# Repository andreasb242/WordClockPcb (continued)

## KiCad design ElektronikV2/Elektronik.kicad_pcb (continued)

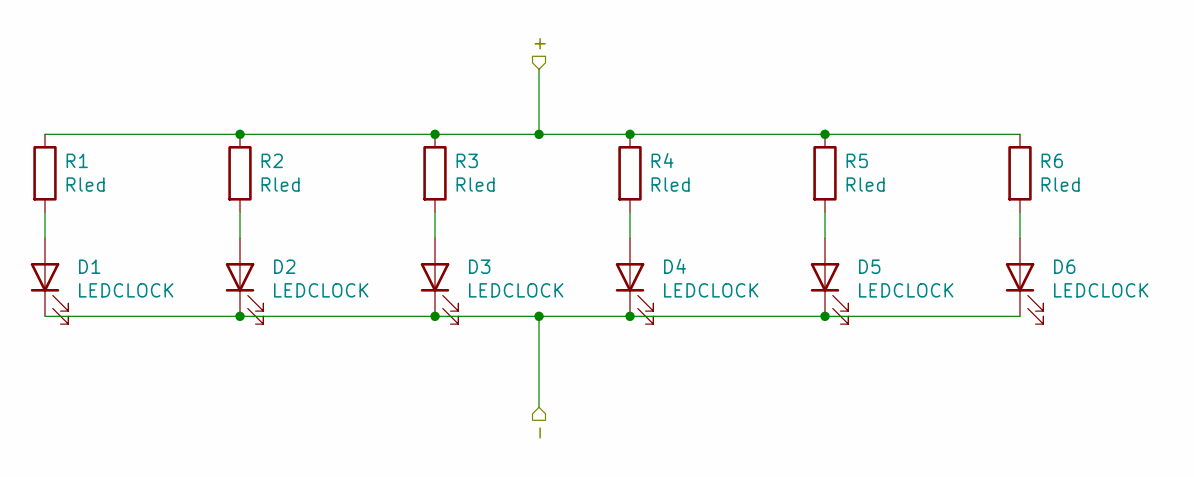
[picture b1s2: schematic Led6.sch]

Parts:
D1, D2, D3, D4, D5, D6: LEDCLOCK; LED_0603_1608Metric
R1, R2, R3, R4, R5, R6: Rled; R_0402_1005Metric

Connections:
/1/1/+: R1.1, R2.1, R3.1, R4.1, R5.1, R6.1; also elsewhere on the board
/1/1/-: D1.1 (K), D2.1 (K), D3.1 (K), D4.1 (K), D5.1 (K), D6.1 (K); also elsewhere on the board
unnamed: D1.2 (A), R1.2
unnamed: D2.2 (A), R2.2
unnamed: D3.2 (A), R3.2
unnamed: D4.2 (A), R4.2
unnamed: D5.2 (A), R5.2
unnamed: D6.2 (A), R6.2

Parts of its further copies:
D7, D8, D9, D10, D11, D12, D13, D14, D15, D16, D17, D18, D19, D20, D21, D22, D23, D24, D25, D26, D27, D28, D29, D30, D31, D32, D33, D34, D35, D36, D37, D38, D39, D40, D41, D42, D43, D44, D45, D46, D47, D48, D49, D50, D51, D52, D53, D54, D55, D56, D57, D58, D59, D60, D61, D62, D63, D64, D65, D66, D67, D68, D69, D70, D71, D72, D73, D74, D75, D76, D77, D78, D79, D80, D81, D82, D83, D84, D85, D86, D87, D88, D89, D90, D91, D92, D93, D94, D95, D96, D97, D98, D99, D100, D101, D102, D103, D104, D105, D106, D107, D108, D109, D110, D111, D112, D113, D114, D115, D116, D117, D118, D119, D120, D121, D122, D123, D124, D125, D126, D127, D128, D129, D130, D131, D132, D133, D134, D135, D136, D137, D138, D139, D140, D141, D142, D143, D144, D145, D146, D147, D148, D149, D150, D151, D152, D153, D154, D155, D156, D157, D158, D159, D160, D161, D162, D163, D164, D165, D166, D167, D168, D169, D170, D171, D172, D173, D174, D175, D176, D177, D178, D179, D180, D181, D182, D183, D184, D185, D186, D187, D188, D189, D190, D191, D192, D193, D194, D195, D196, D197, D198, D199, D200, D201, D202, D203, D204, D205, D206, D207, D208, D209, D210, D211, D212, D213, D214, D215, D216, D217, D218, D219, D220, D221, D222, D223, D224, D225, D226, D227, D228, D229, D230, D231, D232, D233, D234, D235, D236, D237, D238, D239, D240, D241, D242, D243, D244, D245, D246, D247, D248, D249, D250, D251, D252, D253, D254, D255, D256, D257, D258, D259, D260, D261, D262, D263, D264, D265, D266, D267, D268, D269, D270, D271, D272, D273, D274, D275, D276, D277, D278, D279, D280, D281, D282, D283, D284, D285, D286, D287, D288, D289, D290, D291, D292, D293, D294, D295, D296, D297, D298, D299, D300, D301, D302, D303, D304, D305, D306, D307, D308, D309, D310, D311, D312, D313, D314, D315, D316, D317, D318, D319, D320, D321, D322, D323, D324, D325, D326, D327, D328, D329, D330, D331, D332, D333, D334, D335, D336, D337, D338, D339, D340, D341, D342, D343, D344, D345, D346, D347, D348, D349, D350, D351, D352, D353, D354, D355, D356, D357, D358, D359, D360, D361, D362, D363, D364, D365, D366, D367, D368, D369, D370, D371, D372, D373, D374, D375, D376, D377, D378, D379, D380, D381, D382, D383, D384, D385, D386, D387, D388, D389, D390, D391, D392, D393, D394, D395, D396, D397, D398, D399, D400, D401, D402, D403, D404, D405, D406, D407, D408, D409, D410, D411, D412, D413, D414, D415, D416, D417, D418, D419, D420, D421, D422, D423, D424, D425, D426, D427, D428, D429, D430, D431, D432, D433, D434, D435, D436, D437, D438, D439, D440, D441, D442, D443, D444, D445, D446, D447, D448, D449, D450, D451, D452, D453, D454, D455, D456, D457, D458, D459, D460, D461, D462, D463, D464, D465, D466, D467, D468, D469, D470, D471, D472, D473, D474, D475, D476, D477, D478, D479, D480, D481, D482, D483, D484, D485, D486, D487, D488, D489, D490, D491, D492, D493, D494, D495, D496, D497, D498, D499, D500, D501, D502, D503, D504, D505, D506, D507, D508, D509, D510, D511, D512, D513, D514, D515, D516, D517, D518, D519, D520, D521, D522, D523, D524, D525, D526, D527, D528: LEDCLOCK; LED_0603_1608Metric
R7, R8, R9, R10, R11, R12, R13, R14, R15, R16, R17, R18, R19, R20, R21, R22, R23, R24, R25, R26, R27, R28, R29, R30, R31, R32, R33, R34, R35, R36, R37, R38, R39, R40, R41, R42, R43, R44, R45, R46, R47, R48, R49, R50, R51, R52, R53, R54, R55, R56, R57, R58, R59, R60, R61, R62, R63, R64, R65, R66, R67, R68, R69, R70, R71, R72, R73, R74, R75, R76, R77, R78, R79, R80, R81, R82, R83, R84, R85, R86, R87, R88, R89, R90, R91, R92, R93, R94, R95, R96, R97, R98, R99, R100, R101, R102, R103, R104, R105, R106, R107, R108, R109, R110, R111, R112, R113, R114, R115, R116, R117, R118, R119, R120, R121, R122, R123, R124, R125, R126, R127, R128, R129, R130, R131, R132, R133, R134, R135, R136, R137, R138, R139, R140, R141, R142, R143, R144, R145, R146, R147, R148, R149, R150, R151, R152, R153, R154, R155, R156, R157, R158, R159, R160, R161, R162, R163, R164, R165, R166, R167, R168, R169, R170, R171, R172, R173, R174, R175, R176, R177, R178, R179, R180, R181, R182, R183, R184, R185, R186, R187, R188, R189, R190, R191, R192, R193, R194, R195, R196, R197, R198, R199, R200, R201, R202, R203, R204, R205, R206, R207, R208, R209, R210, R211, R212, R213, R214, R215, R216, R217, R218, R219, R220, R221, R222, R223, R224, R225, R226, R227, R228, R229, R230, R231, R232, R233, R234, R235, R236, R237, R238, R239, R240, R241, R242, R243, R244, R245, R246, R247, R248, R249, R250, R251, R252, R253, R254, R255, R256, R257, R258, R259, R260, R261, R262, R263, R264, R265, R266, R267, R268, R269, R270, R271, R272, R273, R274, R275, R276, R277, R278, R279, R280, R281, R282, R283, R284, R285, R286, R287, R288, R289, R290, R291, R292, R293, R294, R295, R296, R297, R298, R299, R300, R301, R302, R303, R304, R305, R306, R307, R308, R309, R310, R311, R312, R313, R314, R315, R316, R317, R318, R319, R320, R321, R322, R323, R324, R325, R326, R327, R328, R329, R330, R331, R332, R333, R334, R335, R336, R337, R338, R339, R340, R341, R342, R343, R344, R345, R346, R347, R348, R349, R350, R351, R352, R353, R354, R355, R356, R357, R358, R359, R360, R361, R362, R363, R364, R365, R366, R367, R368, R369, R370, R371, R372, R373, R374, R375, R376, R377, R378, R379, R380, R381, R382, R383, R384, R385, R386, R387, R388, R389, R390, R391, R392, R393, R394, R395, R396, R397, R398, R399, R400, R401, R402, R403, R404, R405, R406, R407, R408, R409, R410, R411, R412, R413, R414, R415, R416, R417, R418, R419, R420, R421, R422, R423, R424, R425, R426, R427, R428, R429, R430, R431, R432, R433, R434, R435, R436, R437, R438, R439, R440, R441, R442, R443, R444, R445, R446, R447, R448, R449, R450, R451, R452, R453, R454, R455, R456, R457, R458, R459, R460, R461, R462, R463, R464, R465, R466, R467, R468, R469, R470, R471, R472, R473, R474, R475, R476, R477, R478, R479, R480, R481, R482, R483, R484, R485, R486, R487, R488, R489, R490, R491, R492, R493, R494, R495, R496, R497, R498, R499, R500, R501, R502, R503, R504, R505, R506, R507, R508, R509, R510, R511, R512, R513, R514, R515, R516, R517, R518, R519, R520, R521, R522, R523, R524, R525, R526, R527, R528: Rled; R_0402_1005Metric

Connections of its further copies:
/1/1/+: R7.1, R8.1, R9.1, R10.1, R11.1, R12.1, R13.1, R14.1, R15.1, R16.1, R17.1, R18.1, R19.1, R20.1, R21.1, R22.1, R23.1, R24.1, R25.1, R26.1, R27.1, R28.1, R29.1, R30.1, R31.1, R32.1, R33.1, R34.1, R35.1, R36.1, R37.1, R38.1, R39.1, R40.1, R41.1, R42.1, R43.1, R44.1, R45.1, R46.1, R47.1, R48.1, R49.1, R50.1, R51.1, R52.1, R53.1, R54.1; also elsewhere on the board
/1/1/-: D55.1 (K), D56.1 (K), D57.1 (K), D58.1 (K), D59.1 (K), D60.1 (K), D121.1 (K), D122.1 (K), D123.1 (K), D124.1 (K), D125.1 (K), D126.1 (K), D181.1 (K), D182.1 (K), D183.1 (K), D184.1 (K), D185.1 (K), D186.1 (K), D229.1 (K), D230.1 (K), D231.1 (K), D232.1 (K), D233.1 (K), D234.1 (K), D295.1 (K), D296.1 (K), D297.1 (K), D298.1 (K), D299.1 (K), D300.1 (K), D409.1 (K), D410.1 (K), D411.1 (K), D412.1 (K), D413.1 (K), D414.1 (K), D469.1 (K), D470.1 (K), D471.1 (K), D472.1 (K), D473.1 (K), D474.1 (K); also elsewhere on the board
/1/2/+: R55.1, R56.1, R57.1, R58.1, R59.1, R60.1, R61.1, R62.1, R63.1, R64.1, R65.1, R66.1, R67.1, R68.1, R69.1, R70.1, R71.1, R72.1, R73.1, R74.1, R75.1, R76.1, R77.1, R78.1, R79.1, R80.1, R81.1, R82.1, R83.1, R84.1, R85.1, R86.1, R87.1, R88.1, R89.1, R90.1, R91.1, R92.1, R93.1, R94.1, R95.1, R96.1, R97.1, R98.1, R99.1, R100.1, R101.1, R102.1, R103.1, R104.1, R105.1, R106.1, R107.1, R108.1, R109.1, R110.1, R111.1, R112.1, R113.1, R114.1, R115.1, R116.1, R117.1, R118.1, R119.1, R120.1; also elsewhere on the board
/1/3/+: R121.1, R122.1, R123.1, R124.1, R125.1, R126.1, R127.1, R128.1, R129.1, R130.1, R131.1, R132.1, R133.1, R134.1, R135.1, R136.1, R137.1, R138.1, R139.1, R140.1, R141.1, R142.1, R143.1, R144.1, R145.1, R146.1, R147.1, R148.1, R149.1, R150.1, R151.1, R152.1, R153.1, R154.1, R155.1, R156.1, R157.1, R158.1, R159.1, R160.1, R161.1, R162.1, R163.1, R164.1, R165.1, R166.1, R167.1, R168.1, R169.1, R170.1, R171.1, R172.1, R173.1, R174.1, R175.1, R176.1, R177.1, R178.1, R179.1, R180.1; also elsewhere on the board
/1/4/+: R181.1, R182.1, R183.1, R184.1, R185.1, R186.1, R187.1, R188.1, R189.1, R190.1, R191.1, R192.1, R193.1, R194.1, R195.1, R196.1, R197.1, R198.1, R199.1, R200.1, R201.1, R202.1, R203.1, R204.1, R205.1, R206.1, R207.1, R208.1, R209.1, R210.1, R211.1, R212.1, R213.1, R214.1, R215.1, R216.1, R217.1, R218.1, R219.1, R220.1, R221.1, R222.1, R223.1, R224.1, R225.1, R226.1, R227.1, R228.1; also elsewhere on the board
/1/5/+: R229.1, R230.1, R231.1, R232.1, R233.1, R234.1, R235.1, R236.1, R237.1, R238.1, R239.1, R240.1, R241.1, R242.1, R243.1, R244.1, R245.1, R246.1, R247.1, R248.1, R249.1, R250.1, R251.1, R252.1, R253.1, R254.1, R255.1, R256.1, R257.1, R258.1, R259.1, R260.1, R261.1, R262.1, R263.1, R264.1, R265.1, R266.1, R267.1, R268.1, R269.1, R270.1, R271.1, R272.1, R273.1, R274.1, R275.1, R276.1, R277.1, R278.1, R279.1, R280.1, R281.1, R282.1, R283.1, R284.1, R285.1, R286.1, R287.1, R288.1, R289.1, R290.1, R291.1, R292.1, R293.1, R294.1; also elsewhere on the board
/1/6/+: R295.1, R296.1, R297.1, R298.1, R299.1, R300.1, R301.1, R302.1, R303.1, R304.1, R305.1, R306.1, R307.1, R308.1, R309.1, R310.1, R311.1, R312.1, R313.1, R314.1, R315.1, R316.1, R317.1, R318.1, R319.1, R320.1, R321.1, R322.1, R323.1, R324.1, R325.1, R326.1, R327.1, R328.1, R329.1, R330.1, R331.1, R332.1, R333.1, R334.1, R335.1, R336.1, R337.1, R338.1, R339.1, R340.1, R341.1, R342.1, R343.1, R344.1, R345.1, R346.1, R347.1, R348.1, R349.1, R350.1, R351.1, R352.1, R353.1, R354.1; also elsewhere on the board
/1/8/+: R409.1, R410.1, R411.1, R412.1, R413.1, R414.1, R415.1, R416.1, R417.1, R418.1, R419.1, R420.1, R421.1, R422.1, R423.1, R424.1, R425.1, R426.1, R427.1, R428.1, R429.1, R430.1, R431.1, R432.1, R433.1, R434.1, R435.1, R436.1, R437.1, R438.1, R439.1, R440.1, R441.1, R442.1, R443.1, R444.1, R445.1, R446.1, R447.1, R448.1, R449.1, R450.1, R451.1, R452.1, R453.1, R454.1, R455.1, R456.1, R457.1, R458.1, R459.1, R460.1, R461.1, R462.1, R463.1, R464.1, R465.1, R466.1, R467.1, R468.1; also elsewhere on the board
/2/1/-: D7.1 (K), D8.1 (K), D9.1 (K), D10.1 (K), D11.1 (K), D12.1 (K), D61.1 (K), D62.1 (K), D63.1 (K), D64.1 (K), D65.1 (K), D66.1 (K), D127.1 (K), D128.1 (K), D129.1 (K), D130.1 (K), D131.1 (K), D132.1 (K), D187.1 (K), D188.1 (K), D189.1 (K), D190.1 (K), D191.1 (K), D192.1 (K), D235.1 (K), D236.1 (K), D237.1 (K), D238.1 (K), D239.1 (K), D240.1 (K), D301.1 (K), D302.1 (K), D303.1 (K), D304.1 (K), D305.1 (K), D306.1 (K), D415.1 (K), D416.1 (K), D417.1 (K), D418.1 (K), D419.1 (K), D420.1 (K), D475.1 (K), D476.1 (K), D477.1 (K), D478.1 (K), D479.1 (K), D480.1 (K); also elsewhere on the board
/3/2/-: D67.1 (K), D68.1 (K), D69.1 (K), D70.1 (K), D71.1 (K), D72.1 (K), D133.1 (K), D134.1 (K), D135.1 (K), D136.1 (K), D137.1 (K), D138.1 (K), D193.1 (K), D194.1 (K), D195.1 (K), D196.1 (K), D197.1 (K), D198.1 (K), D241.1 (K), D242.1 (K), D243.1 (K), D244.1 (K), D245.1 (K), D246.1 (K), D307.1 (K), D308.1 (K), D309.1 (K), D310.1 (K), D311.1 (K), D312.1 (K), D355.1 (K), D356.1 (K), D357.1 (K), D358.1 (K), D359.1 (K), D360.1 (K), D421.1 (K), D422.1 (K), D423.1 (K), D424.1 (K), D425.1 (K), D426.1 (K), D481.1 (K), D482.1 (K), D483.1 (K), D484.1 (K), D485.1 (K), D486.1 (K); also elsewhere on the board
/4/1/-: D13.1 (K), D14.1 (K), D15.1 (K), D16.1 (K), D17.1 (K), D18.1 (K), D73.1 (K), D74.1 (K), D75.1 (K), D76.1 (K), D77.1 (K), D78.1 (K), D139.1 (K), D140.1 (K), D141.1 (K), D142.1 (K), D143.1 (K), D144.1 (K), D199.1 (K), D200.1 (K), D201.1 (K), D202.1 (K), D203.1 (K), D204.1 (K), D247.1 (K), D248.1 (K), D249.1 (K), D250.1 (K), D251.1 (K), D252.1 (K), D313.1 (K), D314.1 (K), D315.1 (K), D316.1 (K), D317.1 (K), D318.1 (K), D361.1 (K), D362.1 (K), D363.1 (K), D364.1 (K), D365.1 (K), D366.1 (K), D427.1 (K), D428.1 (K), D429.1 (K), D430.1 (K), D431.1 (K), D432.1 (K), D487.1 (K), D488.1 (K), D489.1 (K), D490.1 (K), D491.1 (K), D492.1 (K); also elsewhere on the board
/5/1/-: D19.1 (K), D20.1 (K), D21.1 (K), D22.1 (K), D23.1 (K), D24.1 (K), D79.1 (K), D80.1 (K), D81.1 (K), D82.1 (K), D83.1 (K), D84.1 (K), D145.1 (K), D146.1 (K), D147.1 (K), D148.1 (K), D149.1 (K), D150.1 (K), D253.1 (K), D254.1 (K), D255.1 (K), D256.1 (K), D257.1 (K), D258.1 (K), D319.1 (K), D320.1 (K), D321.1 (K), D322.1 (K), D323.1 (K), D324.1 (K), D367.1 (K), D368.1 (K), D369.1 (K), D370.1 (K), D371.1 (K), D372.1 (K), D433.1 (K), D434.1 (K), D435.1 (K), D436.1 (K), D437.1 (K), D438.1 (K), D493.1 (K), D494.1 (K), D495.1 (K), D496.1 (K), D497.1 (K), D498.1 (K); also elsewhere on the board
/6/1/-: D25.1 (K), D26.1 (K), D27.1 (K), D28.1 (K), D29.1 (K), D30.1 (K), D85.1 (K), D86.1 (K), D87.1 (K), D88.1 (K), D89.1 (K), D90.1 (K), D151.1 (K), D152.1 (K), D153.1 (K), D154.1 (K), D155.1 (K), D156.1 (K), D205.1 (K), D206.1 (K), D207.1 (K), D208.1 (K), D209.1 (K), D210.1 (K), D259.1 (K), D260.1 (K), D261.1 (K), D262.1 (K), D263.1 (K), D264.1 (K), D325.1 (K), D326.1 (K), D327.1 (K), D328.1 (K), D329.1 (K), D330.1 (K), D373.1 (K), D374.1 (K), D375.1 (K), D376.1 (K), D377.1 (K), D378.1 (K), D439.1 (K), D440.1 (K), D441.1 (K), D442.1 (K), D443.1 (K), D444.1 (K), D499.1 (K), D500.1 (K), D501.1 (K), D502.1 (K), D503.1 (K), D504.1 (K); also elsewhere on the board
/7/2/-: D91.1 (K), D92.1 (K), D93.1 (K), D94.1 (K), D95.1 (K), D96.1 (K), D157.1 (K), D158.1 (K), D159.1 (K), D160.1 (K), D161.1 (K), D162.1 (K), D211.1 (K), D212.1 (K), D213.1 (K), D214.1 (K), D215.1 (K), D216.1 (K), D265.1 (K), D266.1 (K), D267.1 (K), D268.1 (K), D269.1 (K), D270.1 (K), D331.1 (K), D332.1 (K), D333.1 (K), D334.1 (K), D335.1 (K), D336.1 (K), D379.1 (K), D380.1 (K), D381.1 (K), D382.1 (K), D383.1 (K), D384.1 (K), D445.1 (K), D446.1 (K), D447.1 (K), D448.1 (K), D449.1 (K), D450.1 (K), D505.1 (K), D506.1 (K), D507.1 (K), D508.1 (K), D509.1 (K), D510.1 (K); also elsewhere on the board
/8/1/-: D31.1 (K), D32.1 (K), D33.1 (K), D34.1 (K), D35.1 (K), D36.1 (K), D97.1 (K), D98.1 (K), D99.1 (K), D100.1 (K), D101.1 (K), D102.1 (K), D217.1 (K), D218.1 (K), D219.1 (K), D220.1 (K), D221.1 (K), D222.1 (K), D271.1 (K), D272.1 (K), D273.1 (K), D274.1 (K), D275.1 (K), D276.1 (K), D337.1 (K), D338.1 (K), D339.1 (K), D340.1 (K), D341.1 (K), D342.1 (K), D385.1 (K), D386.1 (K), D387.1 (K), D388.1 (K), D389.1 (K), D390.1 (K), D451.1 (K), D452.1 (K), D453.1 (K), D454.1 (K), D455.1 (K), D456.1 (K); also elsewhere on the board
/9/1/-: D37.1 (K), D38.1 (K), D39.1 (K), D40.1 (K), D41.1 (K), D42.1 (K), D103.1 (K), D104.1 (K), D105.1 (K), D106.1 (K), D107.1 (K), D108.1 (K), D163.1 (K), D164.1 (K), D165.1 (K), D166.1 (K), D167.1 (K), D168.1 (K), D223.1 (K), D224.1 (K), D225.1 (K), D226.1 (K), D227.1 (K), D228.1 (K), D277.1 (K), D278.1 (K), D279.1 (K), D280.1 (K), D281.1 (K), D282.1 (K), D343.1 (K), D344.1 (K), D345.1 (K), D346.1 (K), D347.1 (K), D348.1 (K), D391.1 (K), D392.1 (K), D393.1 (K), D394.1 (K), D395.1 (K), D396.1 (K), D457.1 (K), D458.1 (K), D459.1 (K), D460.1 (K), D461.1 (K), D462.1 (K), D511.1 (K), D512.1 (K), D513.1 (K), D514.1 (K), D515.1 (K), D516.1 (K); also elsewhere on the board
/10/1/-: D43.1 (K), D44.1 (K), D45.1 (K), D46.1 (K), D47.1 (K), D48.1 (K), D109.1 (K), D110.1 (K), D111.1 (K), D112.1 (K), D113.1 (K), D114.1 (K), D169.1 (K), D170.1 (K), D171.1 (K), D172.1 (K), D173.1 (K), D174.1 (K), D283.1 (K), D284.1 (K), D285.1 (K), D286.1 (K), D287.1 (K), D288.1 (K), D349.1 (K), D350.1 (K), D351.1 (K), D352.1 (K), D353.1 (K), D354.1 (K), D397.1 (K), D398.1 (K), D399.1 (K), D400.1 (K), D401.1 (K), D402.1 (K), D463.1 (K), D464.1 (K), D465.1 (K), D466.1 (K), D467.1 (K), D468.1 (K), D517.1 (K), D518.1 (K), D519.1 (K), D520.1 (K), D521.1 (K), D522.1 (K); also elsewhere on the board
/10/7/+: R355.1, R356.1, R357.1, R358.1, R359.1, R360.1, R361.1, R362.1, R363.1, R364.1, R365.1, R366.1, R367.1, R368.1, R369.1, R370.1, R371.1, R372.1, R373.1, R374.1, R375.1, R376.1, R377.1, R378.1, R379.1, R380.1, R381.1, R382.1, R383.1, R384.1, R385.1, R386.1, R387.1, R388.1, R389.1, R390.1, R391.1, R392.1, R393.1, R394.1, R395.1, R396.1, R397.1, R398.1, R399.1, R400.1, R401.1, R402.1, R403.1, R404.1, R405.1, R406.1, R407.1, R408.1; also elsewhere on the board
/11/1/-: D49.1 (K), D50.1 (K), D51.1 (K), D52.1 (K), D53.1 (K), D54.1 (K), D115.1 (K), D116.1 (K), D117.1 (K), D118.1 (K), D119.1 (K), D120.1 (K), D175.1 (K), D176.1 (K), D177.1 (K), D178.1 (K), D179.1 (K), D180.1 (K), D289.1 (K), D290.1 (K), D291.1 (K), D292.1 (K), D293.1 (K), D294.1 (K), D403.1 (K), D404.1 (K), D405.1 (K), D406.1 (K), D407.1 (K), D408.1 (K), D523.1 (K), D524.1 (K), D525.1 (K), D526.1 (K), D527.1 (K), D528.1 (K); also elsewhere on the board
/sheet605F1288/+: R469.1, R470.1, R471.1, R472.1, R473.1, R474.1, R475.1, R476.1, R477.1, R478.1, R479.1, R480.1, R481.1, R482.1, R483.1, R484.1, R485.1, R486.1, R487.1, R488.1, R489.1, R490.1, R491.1, R492.1, R493.1, R494.1, R495.1, R496.1, R497.1, R498.1, R499.1, R500.1, R501.1, R502.1, R503.1, R504.1, R505.1, R506.1, R507.1, R508.1, R509.1, R510.1, R511.1, R512.1, R513.1, R514.1, R515.1, R516.1, R517.1, R518.1, R519.1, R520.1, R521.1, R522.1, R523.1, R524.1, R525.1, R526.1, R527.1, R528.1; also elsewhere on the board
unnamed: D7.2 (A), R7.2
unnamed: D8.2 (A), R8.2
unnamed: D9.2 (A), R9.2
unnamed: D10.2 (A), R10.2
unnamed: D11.2 (A), R11.2
unnamed: D12.2 (A), R12.2
unnamed: D13.2 (A), R13.2
unnamed: D14.2 (A), R14.2
unnamed: D15.2 (A), R15.2
unnamed: D16.2 (A), R16.2
unnamed: D17.2 (A), R17.2
unnamed: D18.2 (A), R18.2
unnamed: D19.2 (A), R19.2
unnamed: D20.2 (A), R20.2
unnamed: D21.2 (A), R21.2
unnamed: D22.2 (A), R22.2
unnamed: D23.2 (A), R23.2
unnamed: D24.2 (A), R24.2
unnamed: D25.2 (A), R25.2
unnamed: D26.2 (A), R26.2
unnamed: D27.2 (A), R27.2
unnamed: D28.2 (A), R28.2
unnamed: D29.2 (A), R29.2
unnamed: D30.2 (A), R30.2
unnamed: D31.2 (A), R31.2
unnamed: D32.2 (A), R32.2
unnamed: D33.2 (A), R33.2
unnamed: D34.2 (A), R34.2
unnamed: D35.2 (A), R35.2
unnamed: D36.2 (A), R36.2
unnamed: D37.2 (A), R37.2
unnamed: D38.2 (A), R38.2
unnamed: D39.2 (A), R39.2
unnamed: D40.2 (A), R40.2
unnamed: D41.2 (A), R41.2
unnamed: D42.2 (A), R42.2
unnamed: D43.2 (A), R43.2
unnamed: D44.2 (A), R44.2
unnamed: D45.2 (A), R45.2
unnamed: D46.2 (A), R46.2
unnamed: D47.2 (A), R47.2
unnamed: D48.2 (A), R48.2
unnamed: D49.2 (A), R49.2
unnamed: D50.2 (A), R50.2
unnamed: D51.2 (A), R51.2
unnamed: D52.2 (A), R52.2
unnamed: D53.2 (A), R53.2
unnamed: D54.2 (A), R54.2
unnamed: D55.2 (A), R55.2
unnamed: D56.2 (A), R56.2
unnamed: D57.2 (A), R57.2
unnamed: D58.2 (A), R58.2
unnamed: D59.2 (A), R59.2
unnamed: D60.2 (A), R60.2
unnamed: D61.2 (A), R61.2
unnamed: D62.2 (A), R62.2
unnamed: D63.2 (A), R63.2
unnamed: D64.2 (A), R64.2
unnamed: D65.2 (A), R65.2
unnamed: D66.2 (A), R66.2
unnamed: D67.2 (A), R67.2
unnamed: D68.2 (A), R68.2
unnamed: D69.2 (A), R69.2
unnamed: D70.2 (A), R70.2
unnamed: D71.2 (A), R71.2
unnamed: D72.2 (A), R72.2
unnamed: D73.2 (A), R73.2
unnamed: D74.2 (A), R74.2
unnamed: D75.2 (A), R75.2
unnamed: D76.2 (A), R76.2
unnamed: D77.2 (A), R77.2
unnamed: D78.2 (A), R78.2
unnamed: D79.2 (A), R79.2
unnamed: D80.2 (A), R80.2
unnamed: D81.2 (A), R81.2
unnamed: D82.2 (A), R82.2
unnamed: D83.2 (A), R83.2
unnamed: D84.2 (A), R84.2
unnamed: D85.2 (A), R85.2
unnamed: D86.2 (A), R86.2
unnamed: D87.2 (A), R87.2
unnamed: D88.2 (A), R88.2
unnamed: D89.2 (A), R89.2
unnamed: D90.2 (A), R90.2
unnamed: D91.2 (A), R91.2
unnamed: D92.2 (A), R92.2
unnamed: D93.2 (A), R93.2
unnamed: D94.2 (A), R94.2
unnamed: D95.2 (A), R95.2
unnamed: D96.2 (A), R96.2
unnamed: D97.2 (A), R97.2
unnamed: D98.2 (A), R98.2
unnamed: D99.2 (A), R99.2
unnamed: D100.2 (A), R100.2
unnamed: D101.2 (A), R101.2
unnamed: D102.2 (A), R102.2
unnamed: D103.2 (A), R103.2
unnamed: D104.2 (A), R104.2
unnamed: D105.2 (A), R105.2
unnamed: D106.2 (A), R106.2
unnamed: D107.2 (A), R107.2
unnamed: D108.2 (A), R108.2
unnamed: D109.2 (A), R109.2
unnamed: D110.2 (A), R110.2
unnamed: D111.2 (A), R111.2
unnamed: D112.2 (A), R112.2
unnamed: D113.2 (A), R113.2
unnamed: D114.2 (A), R114.2
unnamed: D115.2 (A), R115.2
unnamed: D116.2 (A), R116.2
unnamed: D117.2 (A), R117.2
unnamed: D118.2 (A), R118.2
unnamed: D119.2 (A), R119.2
unnamed: D120.2 (A), R120.2
unnamed: D121.2 (A), R121.2
unnamed: D122.2 (A), R122.2
unnamed: D123.2 (A), R123.2
unnamed: D124.2 (A), R124.2
unnamed: D125.2 (A), R125.2
unnamed: D126.2 (A), R126.2
unnamed: D127.2 (A), R127.2
unnamed: D128.2 (A), R128.2
unnamed: D129.2 (A), R129.2
unnamed: D130.2 (A), R130.2
unnamed: D131.2 (A), R131.2
unnamed: D132.2 (A), R132.2
unnamed: D133.2 (A), R133.2
unnamed: D134.2 (A), R134.2
unnamed: D135.2 (A), R135.2
unnamed: D136.2 (A), R136.2
unnamed: D137.2 (A), R137.2
unnamed: D138.2 (A), R138.2
unnamed: D139.2 (A), R139.2
unnamed: D140.2 (A), R140.2
unnamed: D141.2 (A), R141.2
unnamed: D142.2 (A), R142.2
unnamed: D143.2 (A), R143.2
unnamed: D144.2 (A), R144.2
unnamed: D145.2 (A), R145.2
unnamed: D146.2 (A), R146.2
unnamed: D147.2 (A), R147.2
unnamed: D148.2 (A), R148.2
unnamed: D149.2 (A), R149.2
unnamed: D150.2 (A), R150.2
unnamed: D151.2 (A), R151.2
unnamed: D152.2 (A), R152.2
unnamed: D153.2 (A), R153.2
unnamed: D154.2 (A), R154.2
unnamed: D155.2 (A), R155.2
unnamed: D156.2 (A), R156.2
unnamed: D157.2 (A), R157.2
unnamed: D158.2 (A), R158.2
unnamed: D159.2 (A), R159.2
unnamed: D160.2 (A), R160.2
unnamed: D161.2 (A), R161.2
unnamed: D162.2 (A), R162.2
unnamed: D163.2 (A), R163.2
unnamed: D164.2 (A), R164.2
unnamed: D165.2 (A), R165.2
unnamed: D166.2 (A), R166.2
unnamed: D167.2 (A), R167.2
unnamed: D168.2 (A), R168.2
unnamed: D169.2 (A), R169.2
unnamed: D170.2 (A), R170.2
unnamed: D171.2 (A), R171.2
unnamed: D172.2 (A), R172.2
unnamed: D173.2 (A), R173.2
unnamed: D174.2 (A), R174.2
unnamed: D175.2 (A), R175.2
unnamed: D176.2 (A), R176.2
unnamed: D177.2 (A), R177.2
unnamed: D178.2 (A), R178.2
unnamed: D179.2 (A), R179.2
unnamed: D180.2 (A), R180.2
unnamed: D181.2 (A), R181.2
unnamed: D182.2 (A), R182.2
unnamed: D183.2 (A), R183.2
unnamed: D184.2 (A), R184.2
unnamed: D185.2 (A), R185.2
unnamed: D186.2 (A), R186.2
unnamed: D187.2 (A), R187.2
unnamed: D188.2 (A), R188.2
unnamed: D189.2 (A), R189.2
unnamed: D190.2 (A), R190.2
unnamed: D191.2 (A), R191.2
unnamed: D192.2 (A), R192.2
unnamed: D193.2 (A), R193.2
unnamed: D194.2 (A), R194.2
unnamed: D195.2 (A), R195.2
unnamed: D196.2 (A), R196.2
unnamed: D197.2 (A), R197.2
unnamed: D198.2 (A), R198.2
unnamed: D199.2 (A), R199.2
unnamed: D200.2 (A), R200.2
unnamed: D201.2 (A), R201.2
unnamed: D202.2 (A), R202.2
unnamed: D203.2 (A), R203.2
unnamed: D204.2 (A), R204.2
unnamed: D205.2 (A), R205.2
unnamed: D206.2 (A), R206.2
unnamed: D207.2 (A), R207.2
unnamed: D208.2 (A), R208.2
unnamed: D209.2 (A), R209.2
unnamed: D210.2 (A), R210.2
unnamed: D211.2 (A), R211.2
unnamed: D212.2 (A), R212.2
unnamed: D213.2 (A), R213.2
unnamed: D214.2 (A), R214.2
unnamed: D215.2 (A), R215.2
unnamed: D216.2 (A), R216.2
unnamed: D217.2 (A), R217.2
unnamed: D218.2 (A), R218.2
unnamed: D219.2 (A), R219.2
unnamed: D220.2 (A), R220.2
unnamed: D221.2 (A), R221.2
unnamed: D222.2 (A), R222.2
unnamed: D223.2 (A), R223.2
unnamed: D224.2 (A), R224.2
unnamed: D225.2 (A), R225.2
unnamed: D226.2 (A), R226.2
unnamed: D227.2 (A), R227.2
unnamed: D228.2 (A), R228.2
unnamed: D229.2 (A), R229.2
unnamed: D230.2 (A), R230.2
unnamed: D231.2 (A), R231.2
unnamed: D232.2 (A), R232.2
unnamed: D233.2 (A), R233.2
unnamed: D234.2 (A), R234.2
unnamed: D235.2 (A), R235.2
unnamed: D236.2 (A), R236.2
unnamed: D237.2 (A), R237.2
unnamed: D238.2 (A), R238.2
unnamed: D239.2 (A), R239.2
unnamed: D240.2 (A), R240.2
unnamed: D241.2 (A), R241.2
unnamed: D242.2 (A), R242.2
unnamed: D243.2 (A), R243.2
unnamed: D244.2 (A), R244.2
unnamed: D245.2 (A), R245.2
unnamed: D246.2 (A), R246.2
unnamed: D247.2 (A), R247.2
unnamed: D248.2 (A), R248.2
unnamed: D249.2 (A), R249.2
unnamed: D250.2 (A), R250.2
unnamed: D251.2 (A), R251.2
unnamed: D252.2 (A), R252.2
unnamed: D253.2 (A), R253.2
unnamed: D254.2 (A), R254.2
unnamed: D255.2 (A), R255.2
unnamed: D256.2 (A), R256.2
unnamed: D257.2 (A), R257.2
unnamed: D258.2 (A), R258.2
unnamed: D259.2 (A), R259.2
unnamed: D260.2 (A), R260.2
unnamed: D261.2 (A), R261.2
unnamed: D262.2 (A), R262.2
unnamed: D263.2 (A), R263.2
unnamed: D264.2 (A), R264.2
unnamed: D265.2 (A), R265.2
unnamed: D266.2 (A), R266.2
unnamed: D267.2 (A), R267.2
unnamed: D268.2 (A), R268.2
unnamed: D269.2 (A), R269.2
unnamed: D270.2 (A), R270.2
unnamed: D271.2 (A), R271.2
unnamed: D272.2 (A), R272.2
unnamed: D273.2 (A), R273.2
unnamed: D274.2 (A), R274.2
unnamed: D275.2 (A), R275.2
unnamed: D276.2 (A), R276.2
unnamed: D277.2 (A), R277.2
unnamed: D278.2 (A), R278.2
unnamed: D279.2 (A), R279.2
unnamed: D280.2 (A), R280.2
unnamed: D281.2 (A), R281.2
unnamed: D282.2 (A), R282.2
unnamed: D283.2 (A), R283.2
unnamed: D284.2 (A), R284.2
unnamed: D285.2 (A), R285.2
unnamed: D286.2 (A), R286.2
unnamed: D287.2 (A), R287.2
unnamed: D288.2 (A), R288.2
unnamed: D289.2 (A), R289.2
unnamed: D290.2 (A), R290.2
unnamed: D291.2 (A), R291.2
unnamed: D292.2 (A), R292.2
unnamed: D293.2 (A), R293.2
unnamed: D294.2 (A), R294.2
unnamed: D295.2 (A), R295.2
unnamed: D296.2 (A), R296.2
unnamed: D297.2 (A), R297.2
unnamed: D298.2 (A), R298.2
unnamed: D299.2 (A), R299.2
unnamed: D300.2 (A), R300.2
unnamed: D301.2 (A), R301.2
unnamed: D302.2 (A), R302.2
unnamed: D303.2 (A), R303.2
unnamed: D304.2 (A), R304.2
unnamed: D305.2 (A), R305.2
unnamed: D306.2 (A), R306.2
unnamed: D307.2 (A), R307.2
unnamed: D308.2 (A), R308.2
unnamed: D309.2 (A), R309.2
unnamed: D310.2 (A), R310.2
unnamed: D311.2 (A), R311.2
unnamed: D312.2 (A), R312.2
unnamed: D313.2 (A), R313.2
unnamed: D314.2 (A), R314.2
unnamed: D315.2 (A), R315.2
unnamed: D316.2 (A), R316.2
unnamed: D317.2 (A), R317.2
unnamed: D318.2 (A), R318.2
unnamed: D319.2 (A), R319.2
unnamed: D320.2 (A), R320.2
unnamed: D321.2 (A), R321.2
unnamed: D322.2 (A), R322.2
unnamed: D323.2 (A), R323.2
unnamed: D324.2 (A), R324.2
unnamed: D325.2 (A), R325.2
unnamed: D326.2 (A), R326.2
unnamed: D327.2 (A), R327.2
unnamed: D328.2 (A), R328.2
unnamed: D329.2 (A), R329.2
unnamed: D330.2 (A), R330.2
unnamed: D331.2 (A), R331.2
unnamed: D332.2 (A), R332.2
unnamed: D333.2 (A), R333.2
unnamed: D334.2 (A), R334.2
unnamed: D335.2 (A), R335.2
unnamed: D336.2 (A), R336.2
unnamed: D337.2 (A), R337.2
unnamed: D338.2 (A), R338.2
unnamed: D339.2 (A), R339.2
unnamed: D340.2 (A), R340.2
unnamed: D341.2 (A), R341.2
unnamed: D342.2 (A), R342.2
unnamed: D343.2 (A), R343.2
unnamed: D344.2 (A), R344.2
unnamed: D345.2 (A), R345.2
unnamed: D346.2 (A), R346.2
unnamed: D347.2 (A), R347.2
unnamed: D348.2 (A), R348.2
unnamed: D349.2 (A), R349.2
unnamed: D350.2 (A), R350.2
unnamed: D351.2 (A), R351.2
unnamed: D352.2 (A), R352.2
unnamed: D353.2 (A), R353.2
unnamed: D354.2 (A), R354.2
unnamed: D355.2 (A), R355.2
unnamed: D356.2 (A), R356.2
unnamed: D357.2 (A), R357.2
unnamed: D358.2 (A), R358.2
unnamed: D359.2 (A), R359.2
unnamed: D360.2 (A), R360.2
unnamed: D361.2 (A), R361.2
unnamed: D362.2 (A), R362.2
unnamed: D363.2 (A), R363.2
unnamed: D364.2 (A), R364.2
unnamed: D365.2 (A), R365.2
unnamed: D366.2 (A), R366.2
unnamed: D367.2 (A), R367.2
unnamed: D368.2 (A), R368.2
unnamed: D369.2 (A), R369.2
unnamed: D370.2 (A), R370.2
unnamed: D371.2 (A), R371.2
unnamed: D372.2 (A), R372.2
unnamed: D373.2 (A), R373.2
unnamed: D374.2 (A), R374.2
unnamed: D375.2 (A), R375.2
unnamed: D376.2 (A), R376.2
unnamed: D377.2 (A), R377.2
unnamed: D378.2 (A), R378.2
unnamed: D379.2 (A), R379.2
unnamed: D380.2 (A), R380.2
unnamed: D381.2 (A), R381.2
unnamed: D382.2 (A), R382.2
unnamed: D383.2 (A), R383.2
unnamed: D384.2 (A), R384.2
unnamed: D385.2 (A), R385.2
unnamed: D386.2 (A), R386.2
unnamed: D387.2 (A), R387.2
unnamed: D388.2 (A), R388.2
unnamed: D389.2 (A), R389.2
unnamed: D390.2 (A), R390.2
unnamed: D391.2 (A), R391.2
unnamed: D392.2 (A), R392.2
unnamed: D393.2 (A), R393.2
unnamed: D394.2 (A), R394.2
unnamed: D395.2 (A), R395.2
unnamed: D396.2 (A), R396.2
unnamed: D397.2 (A), R397.2
unnamed: D398.2 (A), R398.2
unnamed: D399.2 (A), R399.2
unnamed: D400.2 (A), R400.2
unnamed: D401.2 (A), R401.2
unnamed: D402.2 (A), R402.2
unnamed: D403.2 (A), R403.2
unnamed: D404.2 (A), R404.2
unnamed: D405.2 (A), R405.2
unnamed: D406.2 (A), R406.2
unnamed: D407.2 (A), R407.2
unnamed: D408.2 (A), R408.2
unnamed: D409.2 (A), R409.2
unnamed: D410.2 (A), R410.2
unnamed: D411.2 (A), R411.2
unnamed: D412.2 (A), R412.2
unnamed: D413.2 (A), R413.2
unnamed: D414.2 (A), R414.2
unnamed: D415.2 (A), R415.2
unnamed: D416.2 (A), R416.2
unnamed: D417.2 (A), R417.2
unnamed: D418.2 (A), R418.2
unnamed: D419.2 (A), R419.2
unnamed: D420.2 (A), R420.2
unnamed: D421.2 (A), R421.2
unnamed: D422.2 (A), R422.2
unnamed: D423.2 (A), R423.2
unnamed: D424.2 (A), R424.2
unnamed: D425.2 (A), R425.2
unnamed: D426.2 (A), R426.2
unnamed: D427.2 (A), R427.2
unnamed: D428.2 (A), R428.2
unnamed: D429.2 (A), R429.2
unnamed: D430.2 (A), R430.2
unnamed: D431.2 (A), R431.2
unnamed: D432.2 (A), R432.2
unnamed: D433.2 (A), R433.2
unnamed: D434.2 (A), R434.2
unnamed: D435.2 (A), R435.2
unnamed: D436.2 (A), R436.2
unnamed: D437.2 (A), R437.2
unnamed: D438.2 (A), R438.2
unnamed: D439.2 (A), R439.2
unnamed: D440.2 (A), R440.2
unnamed: D441.2 (A), R441.2
unnamed: D442.2 (A), R442.2
unnamed: D443.2 (A), R443.2
unnamed: D444.2 (A), R444.2
unnamed: D445.2 (A), R445.2
unnamed: D446.2 (A), R446.2
unnamed: D447.2 (A), R447.2
unnamed: D448.2 (A), R448.2
unnamed: D449.2 (A), R449.2
unnamed: D450.2 (A), R450.2
unnamed: D451.2 (A), R451.2
unnamed: D452.2 (A), R452.2
unnamed: D453.2 (A), R453.2
unnamed: D454.2 (A), R454.2
unnamed: D455.2 (A), R455.2
unnamed: D456.2 (A), R456.2
unnamed: D457.2 (A), R457.2
unnamed: D458.2 (A), R458.2
unnamed: D459.2 (A), R459.2
unnamed: D460.2 (A), R460.2
unnamed: D461.2 (A), R461.2
unnamed: D462.2 (A), R462.2
unnamed: D463.2 (A), R463.2
unnamed: D464.2 (A), R464.2
unnamed: D465.2 (A), R465.2
unnamed: D466.2 (A), R466.2
unnamed: D467.2 (A), R467.2
unnamed: D468.2 (A), R468.2
unnamed: D469.2 (A), R469.2
unnamed: D470.2 (A), R470.2
unnamed: D471.2 (A), R471.2
unnamed: D472.2 (A), R472.2
unnamed: D473.2 (A), R473.2
unnamed: D474.2 (A), R474.2
unnamed: D475.2 (A), R475.2
unnamed: D476.2 (A), R476.2
unnamed: D477.2 (A), R477.2
unnamed: D478.2 (A), R478.2
unnamed: D479.2 (A), R479.2
unnamed: D480.2 (A), R480.2
unnamed: D481.2 (A), R481.2
unnamed: D482.2 (A), R482.2
unnamed: D483.2 (A), R483.2
unnamed: D484.2 (A), R484.2
unnamed: D485.2 (A), R485.2
unnamed: D486.2 (A), R486.2
unnamed: D487.2 (A), R487.2
unnamed: D488.2 (A), R488.2
unnamed: D489.2 (A), R489.2
unnamed: D490.2 (A), R490.2
unnamed: D491.2 (A), R491.2
unnamed: D492.2 (A), R492.2
unnamed: D493.2 (A), R493.2
unnamed: D494.2 (A), R494.2
unnamed: D495.2 (A), R495.2
unnamed: D496.2 (A), R496.2
unnamed: D497.2 (A), R497.2
unnamed: D498.2 (A), R498.2
unnamed: D499.2 (A), R499.2
unnamed: D500.2 (A), R500.2
unnamed: D501.2 (A), R501.2
unnamed: D502.2 (A), R502.2
unnamed: D503.2 (A), R503.2
unnamed: D504.2 (A), R504.2
unnamed: D505.2 (A), R505.2
unnamed: D506.2 (A), R506.2
unnamed: D507.2 (A), R507.2
unnamed: D508.2 (A), R508.2
unnamed: D509.2 (A), R509.2
unnamed: D510.2 (A), R510.2
unnamed: D511.2 (A), R511.2
unnamed: D512.2 (A), R512.2
unnamed: D513.2 (A), R513.2
unnamed: D514.2 (A), R514.2
unnamed: D515.2 (A), R515.2
unnamed: D516.2 (A), R516.2
unnamed: D517.2 (A), R517.2
unnamed: D518.2 (A), R518.2
unnamed: D519.2 (A), R519.2
unnamed: D520.2 (A), R520.2
unnamed: D521.2 (A), R521.2
unnamed: D522.2 (A), R522.2
unnamed: D523.2 (A), R523.2
unnamed: D524.2 (A), R524.2
unnamed: D525.2 (A), R525.2
unnamed: D526.2 (A), R526.2
unnamed: D527.2 (A), R527.2
unnamed: D528.2 (A), R528.2

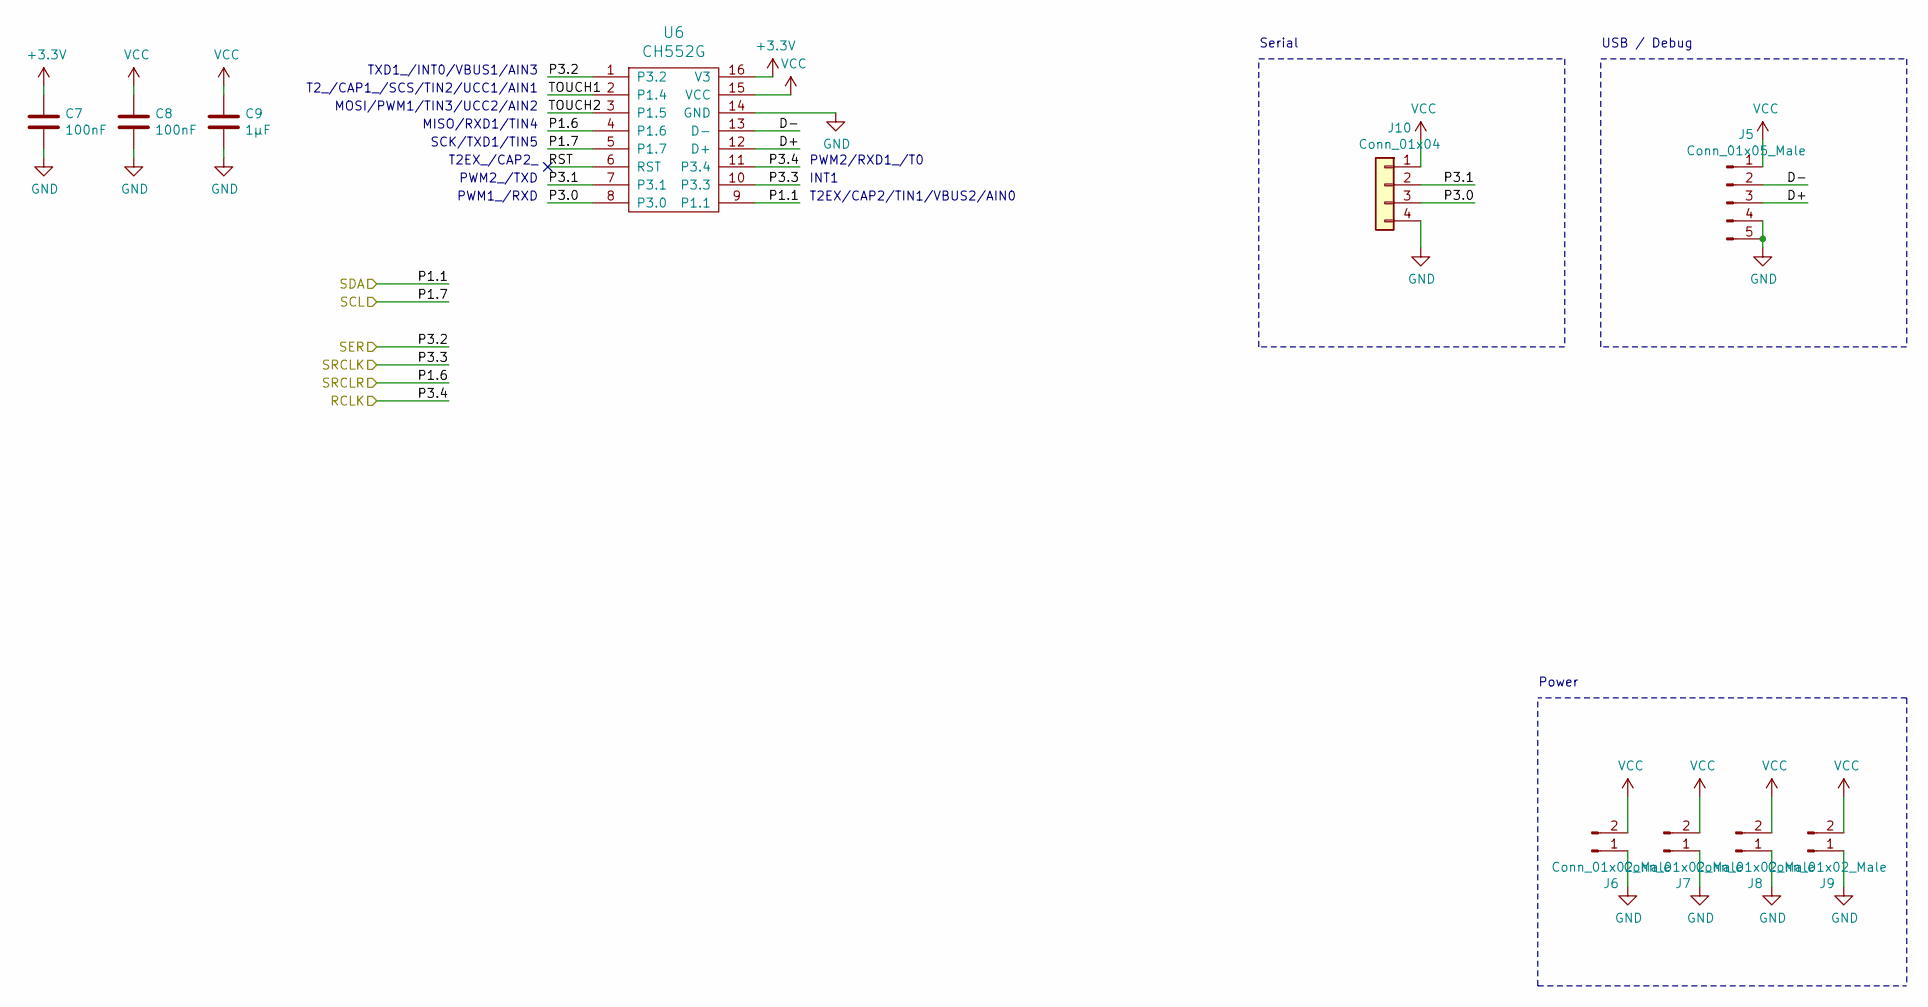
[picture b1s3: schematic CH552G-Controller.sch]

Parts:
C7, C8: 100nF; C_0603_1608Metric
C9: 1µF; C_0603_1608Metric
J5: Conn_01x05_Male; PinHeader_1x05_P2.54mm_Vertical
J6, J7, J8, J9: Conn_01x02_Male; PinHeader_1x02_P2.54mm_Vertical
J10: Conn_01x04; PinHeader_1x04_P2.54mm_Vertical
U6: CH552G; SOP-16_4.4x10.4mm_P1.27mm

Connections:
+3V3: C7.1, U6.16 (V3)
/CH552G-Controller/D+: J5.3, U6.12 (D+)
/CH552G-Controller/D-: J5.2, U6.13 (D-)
/CH552G-Controller/P3.0: J10.3, U6.8 (P3.0)
/CH552G-Controller/P3.1: J10.2, U6.7 (P3.1)
/CH552G-Controller/TOUCH1: U6.2 (P1.4)
/CH552G-Controller/TOUCH2: U6.3 (P1.5)
/RCLK: U6.11 (P3.4); also elsewhere on the board
/SCL: U6.5 (P1.7); also elsewhere on the board
/SDA: U6.9 (P1.1); also elsewhere on the board
/SER: U6.1 (P3.2); also elsewhere on the board
/SRCLK: U6.10 (P3.3); also elsewhere on the board
/SRCLR: U6.4 (P1.6); also elsewhere on the board
GND: C7.2, C8.2, C9.2, J5.4, J5.5, J6.1, J7.1, J8.1, J9.1, J10.4, U6.14 (GND); also elsewhere on the board
VCC: C8.1, C9.1, J5.1, J6.2, J7.2, J8.2, J9.2, J10.1, U6.15 (VCC); also elsewhere on the board

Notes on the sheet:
PWM2/RXD1_/T0
INT1
T2EX/CAP2/TIN1/VBUS2/AIN0
TXD1_/INT0/VBUS1/AIN3
T2_/CAP1_/SCS/TIN2/UCC1/AIN1
MOSI/PWM1/TIN3/UCC2/AIN2
MISO/RXD1/TIN4
SCK/TXD1/TIN5
T2EX_/CAP2_
PWM2_/TXD
PWM1_/RXD
USB / Debug
Power
Serial
